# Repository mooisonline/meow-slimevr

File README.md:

## MeowSlime PCB

## Project
Outdated slime vr tracker pcbs (currently being reworked). 
For BNO085 and Wemos d1.
These don't have a connection for an extension pcb.
Approx 70mm x 36mm (want to make these smaller)

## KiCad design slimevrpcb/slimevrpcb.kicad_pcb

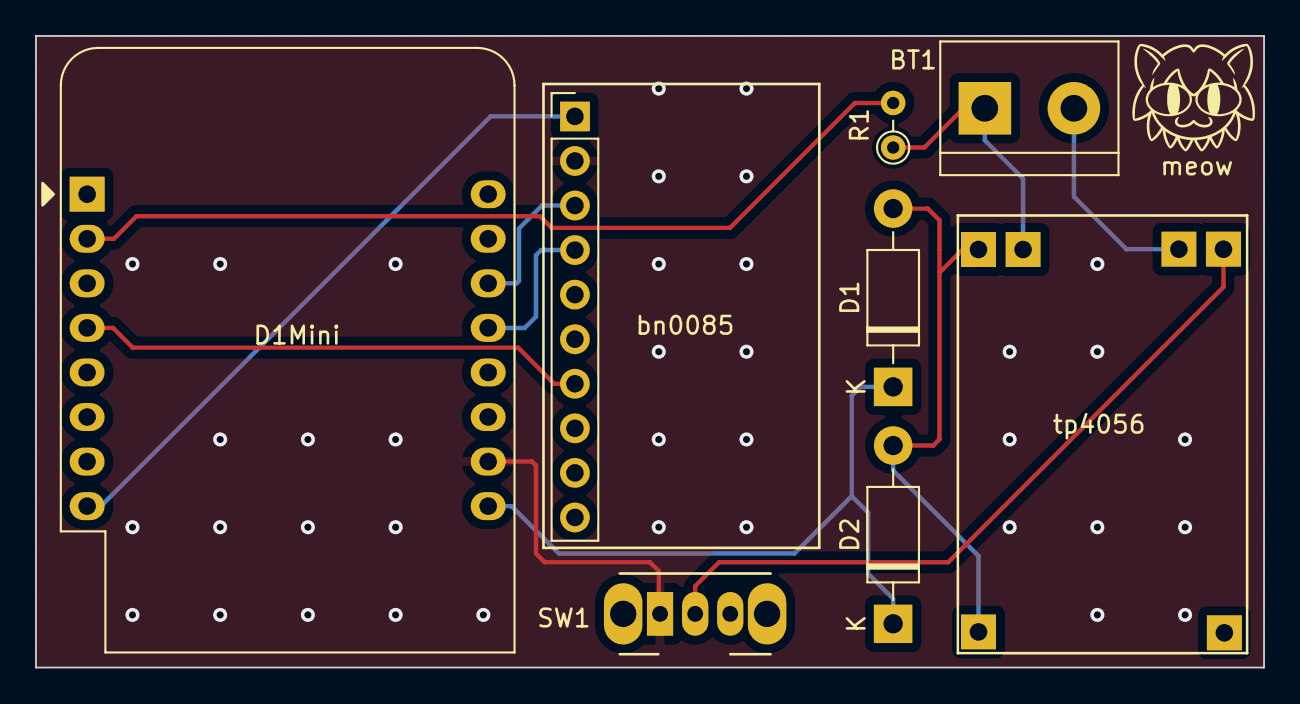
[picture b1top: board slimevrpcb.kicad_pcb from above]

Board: 2 copper layers, 70.0 x 36.0 mm, 8 parts (0 on the bottom side), 11 nets.

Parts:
BT1: Battery; TerminalBlock_bornier-2_P5.08mm
D1, D2: 1N5817; D_DO-41_SOD81_P10.16mm_Horizontal
D1Mini: WeMos_D1_mini; WEMOS_D1_mini_light
R1: 180k; R_Axial_DIN0204_L3.6mm_D1.6mm_P2.54mm_Vertical
SW1: SW_Push; SW_CuK_OS102011MA1QN1_SPDT_Angled
bn0085: Conn_01x10_Pin; PinHeader_1x10_P2.54mm_Vertical
tp4056: TP4056 edited; TP4056

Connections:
3.3v: D1Mini.8 (3V3), bn0085.1 (vcc)
unnamed: BT1.1 (+), R1.1, tp4056.2 (bat+)
unnamed: BT1.2 (-), tp4056.3 (bat-)
unnamed: D1.2 (A), D2.2 (A), tp4056.1 (out+), tp4056.5 (+)
unnamed: D1.1 (K), D1Mini.9 (5V), D2.1 (K)
unnamed: SW1.2 (B), tp4056.4 (out-)
unnamed: D1Mini.2 (A0), R1.2
gnd: D1Mini.10 (GND), SW1.1 (A), bn0085.2 (gnd)
int: D1Mini.4 (SCK/D5), bn0085.7 (int)
scl: D1Mini.14 (SCL/D1), bn0085.3 (scl)
sda: D1Mini.13 (SDA/D2), bn0085.4 (sda)

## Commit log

2024-08-19 meowslime
